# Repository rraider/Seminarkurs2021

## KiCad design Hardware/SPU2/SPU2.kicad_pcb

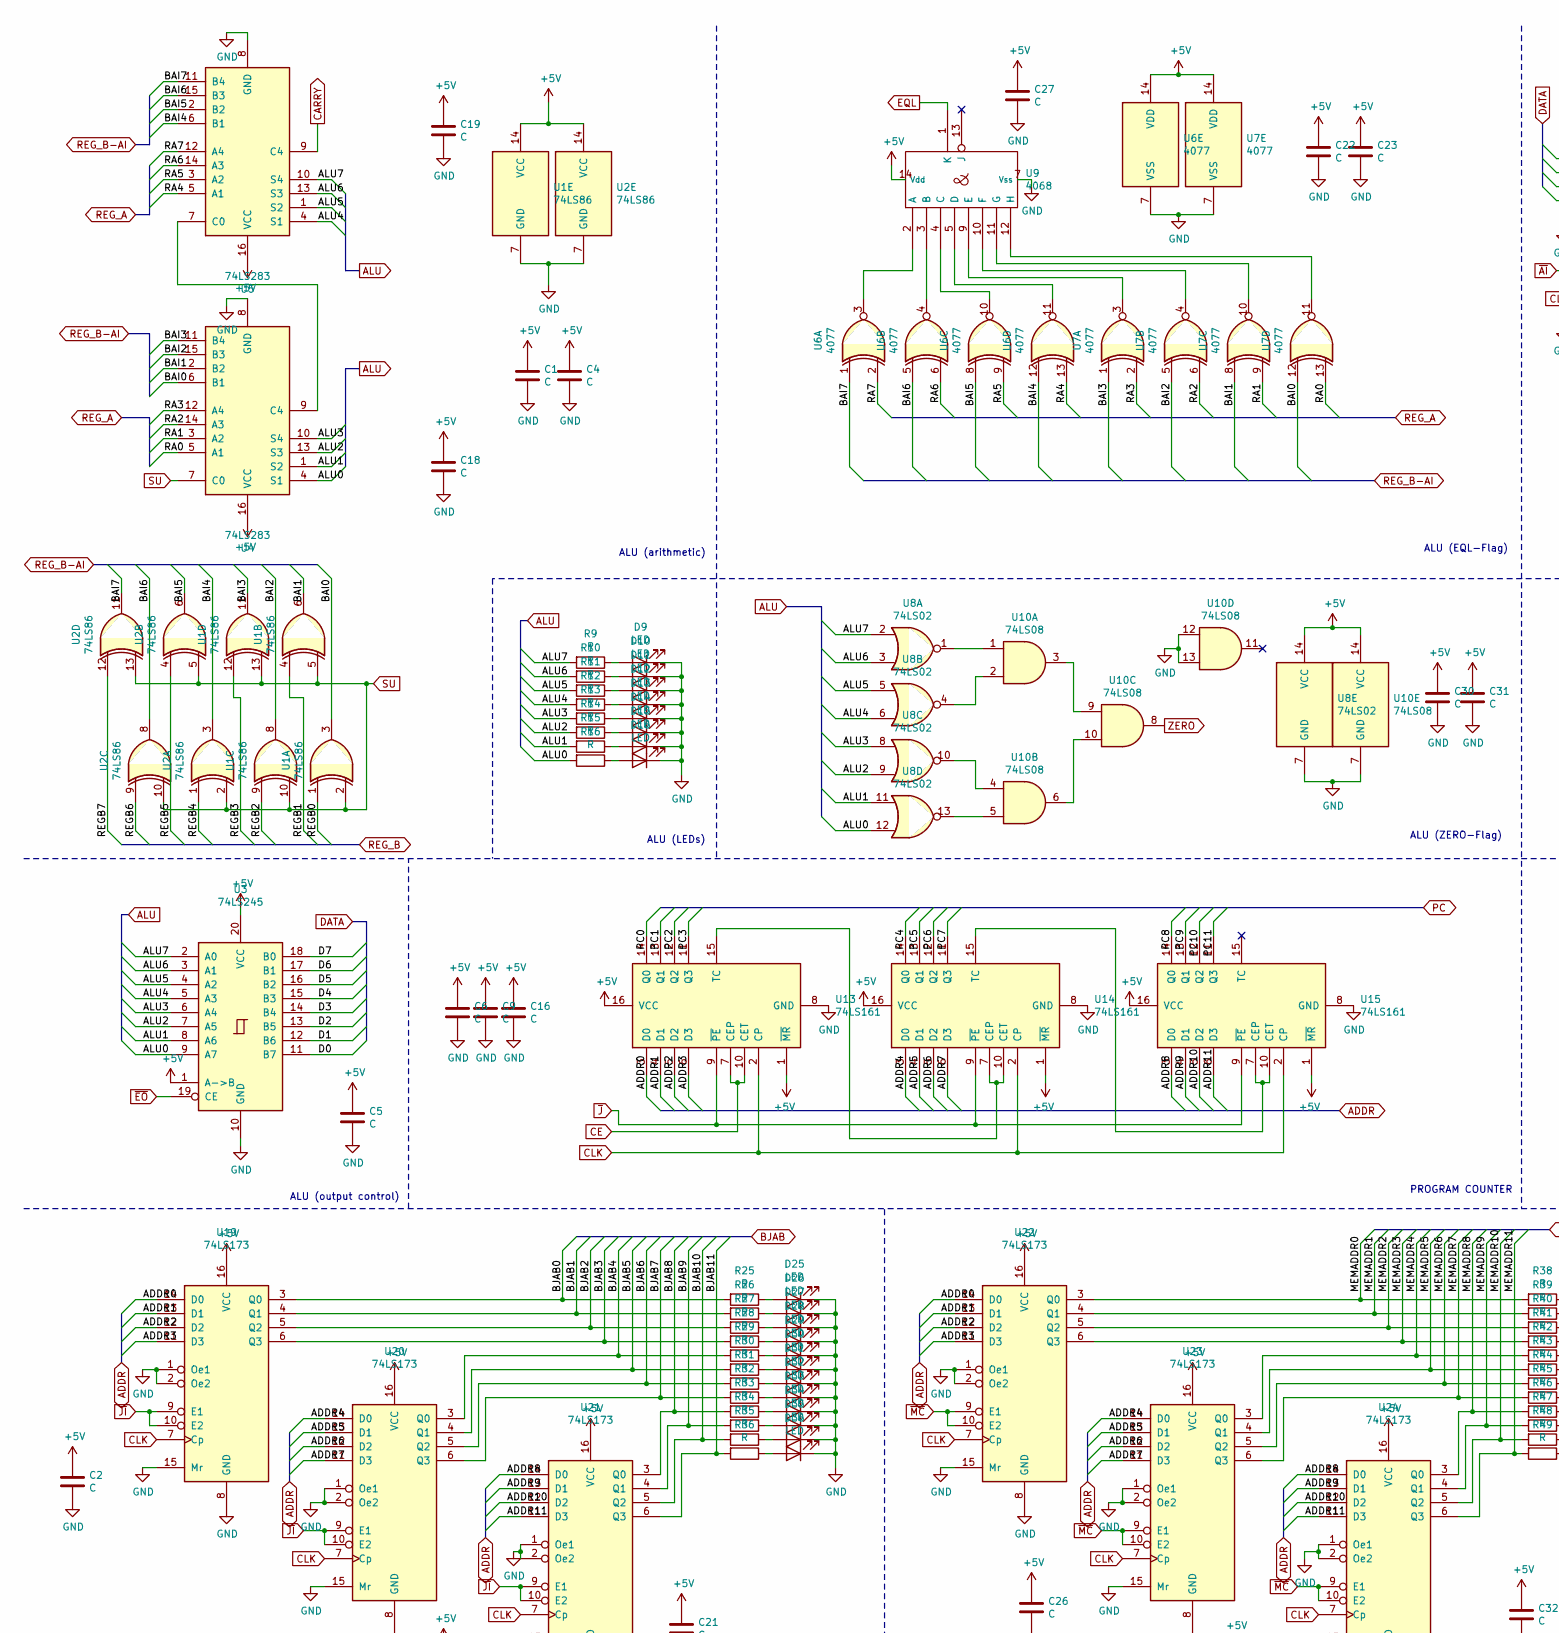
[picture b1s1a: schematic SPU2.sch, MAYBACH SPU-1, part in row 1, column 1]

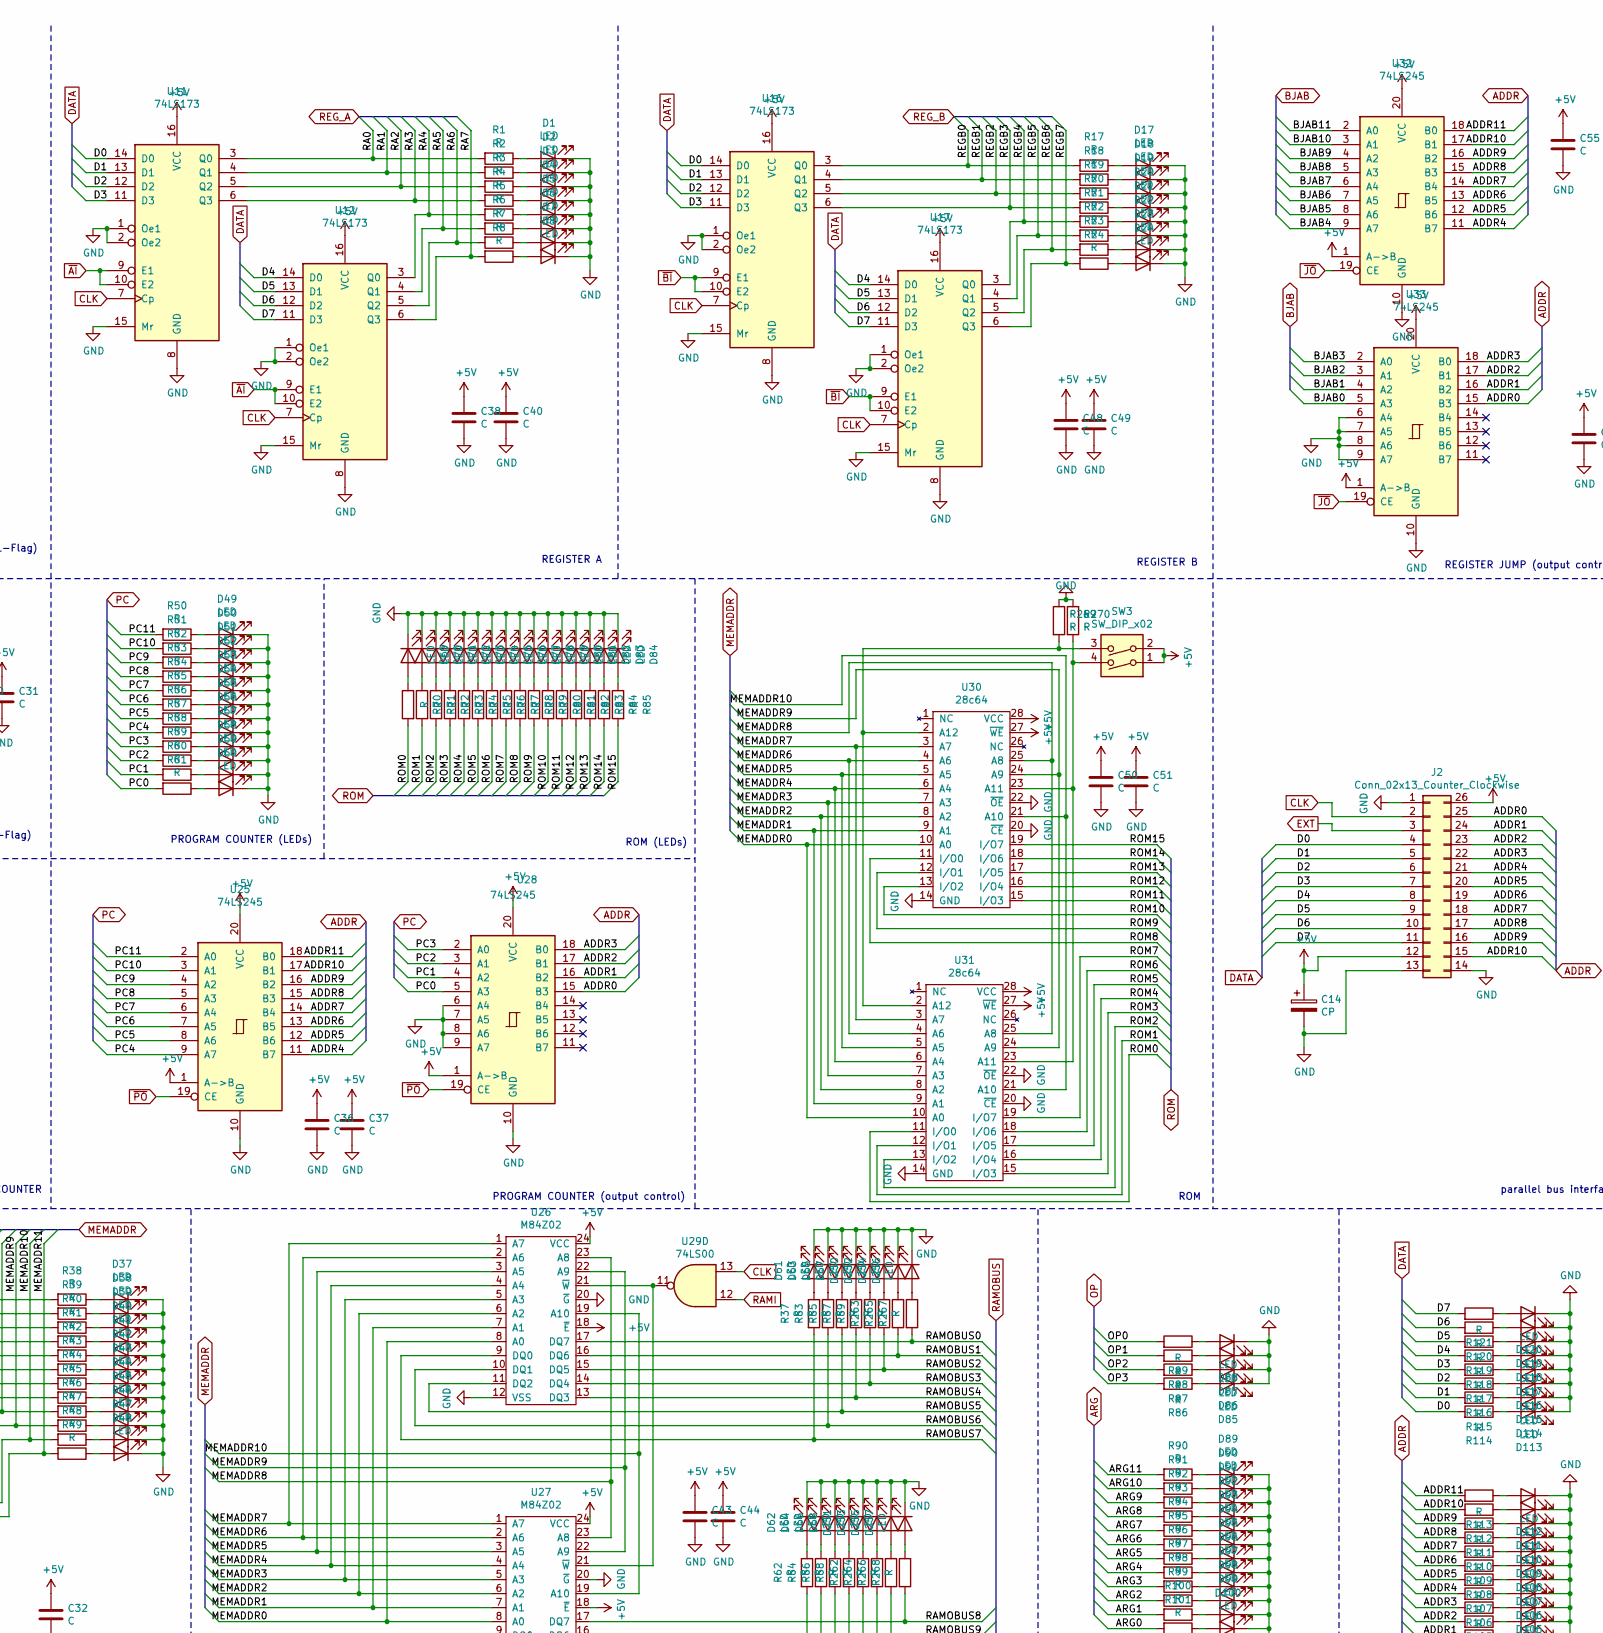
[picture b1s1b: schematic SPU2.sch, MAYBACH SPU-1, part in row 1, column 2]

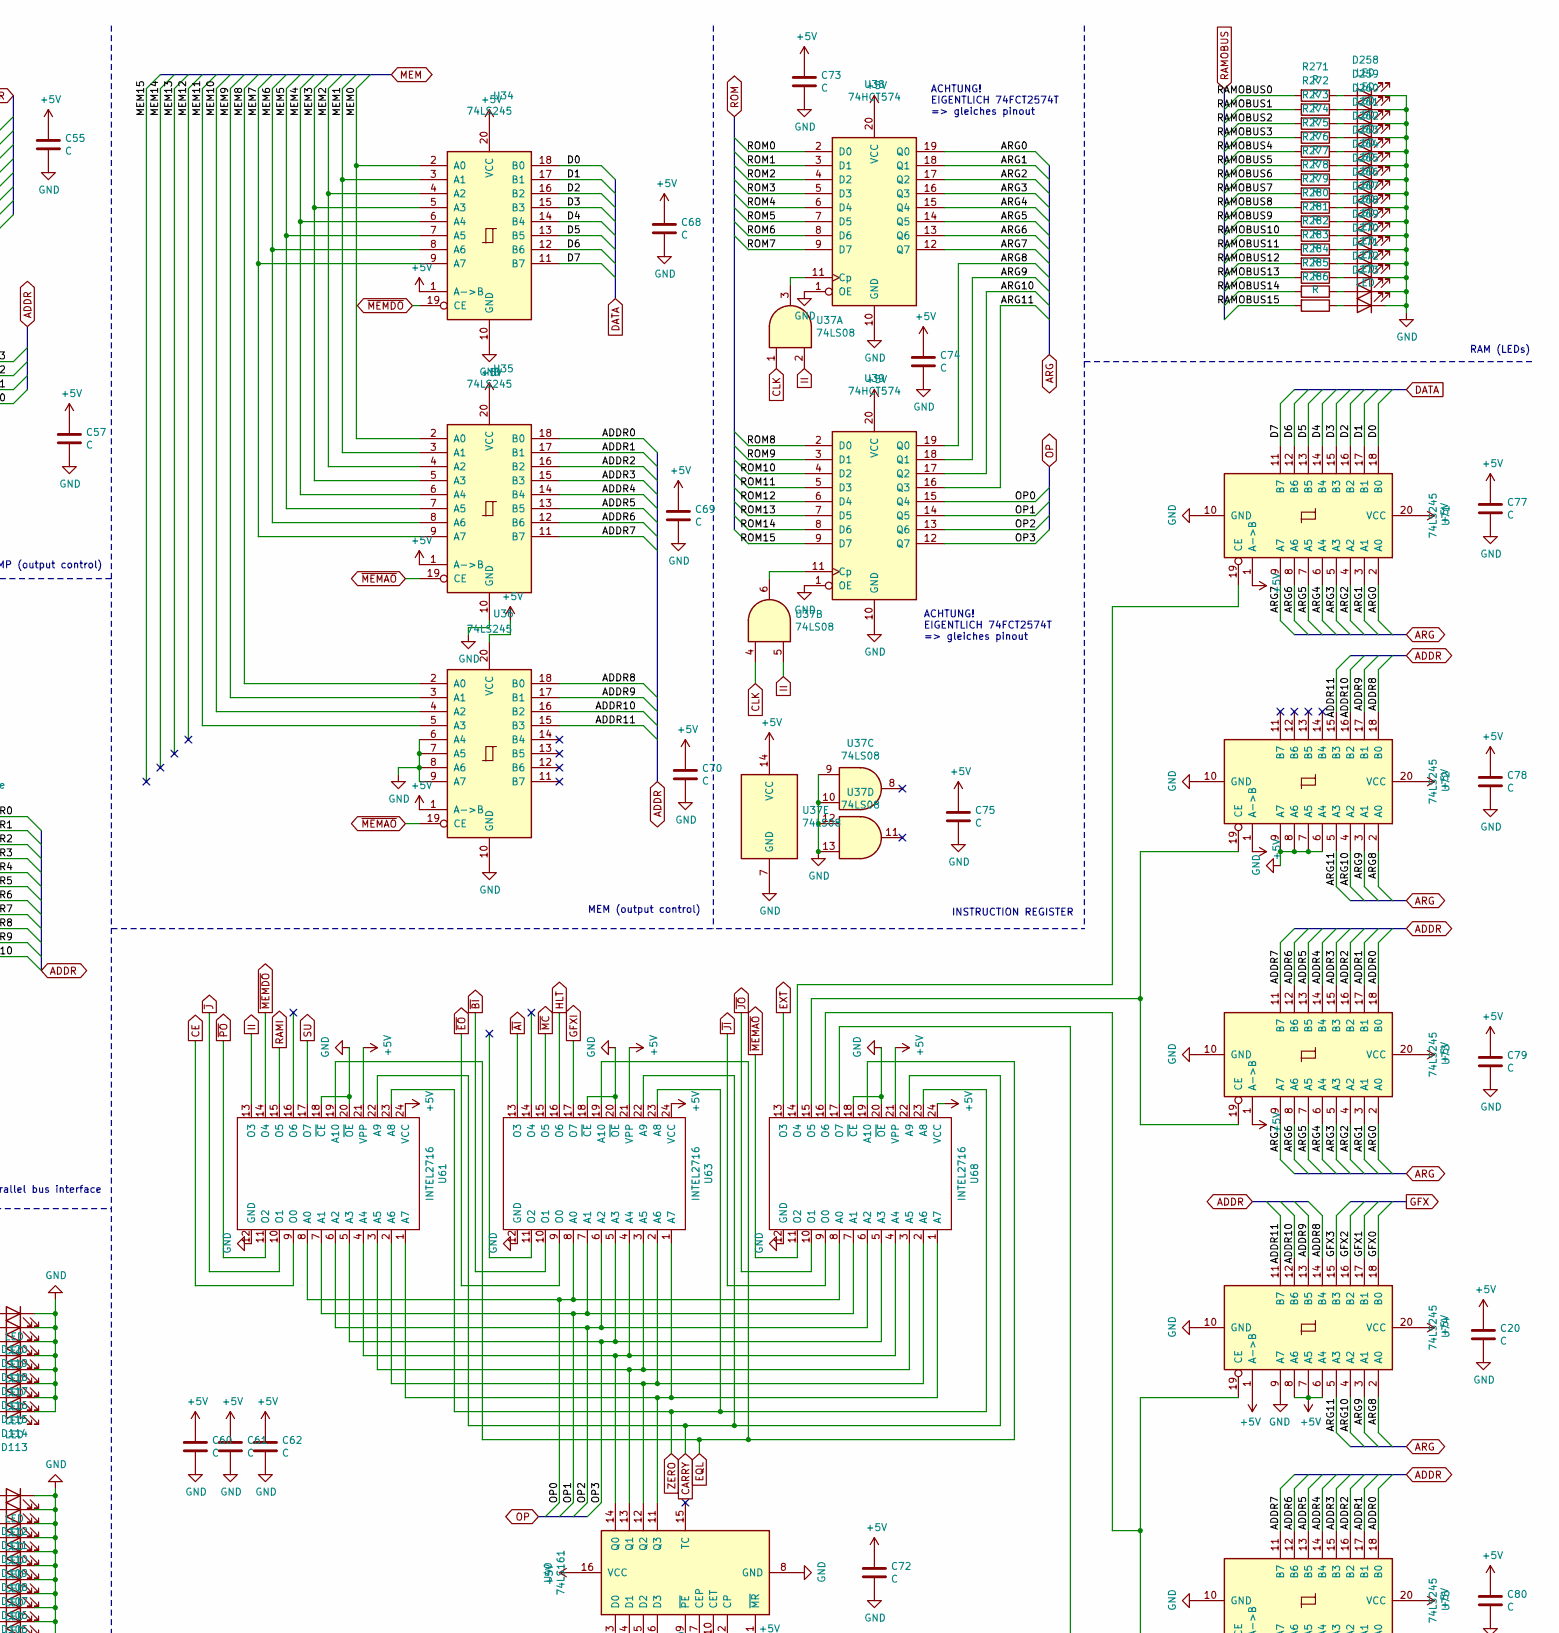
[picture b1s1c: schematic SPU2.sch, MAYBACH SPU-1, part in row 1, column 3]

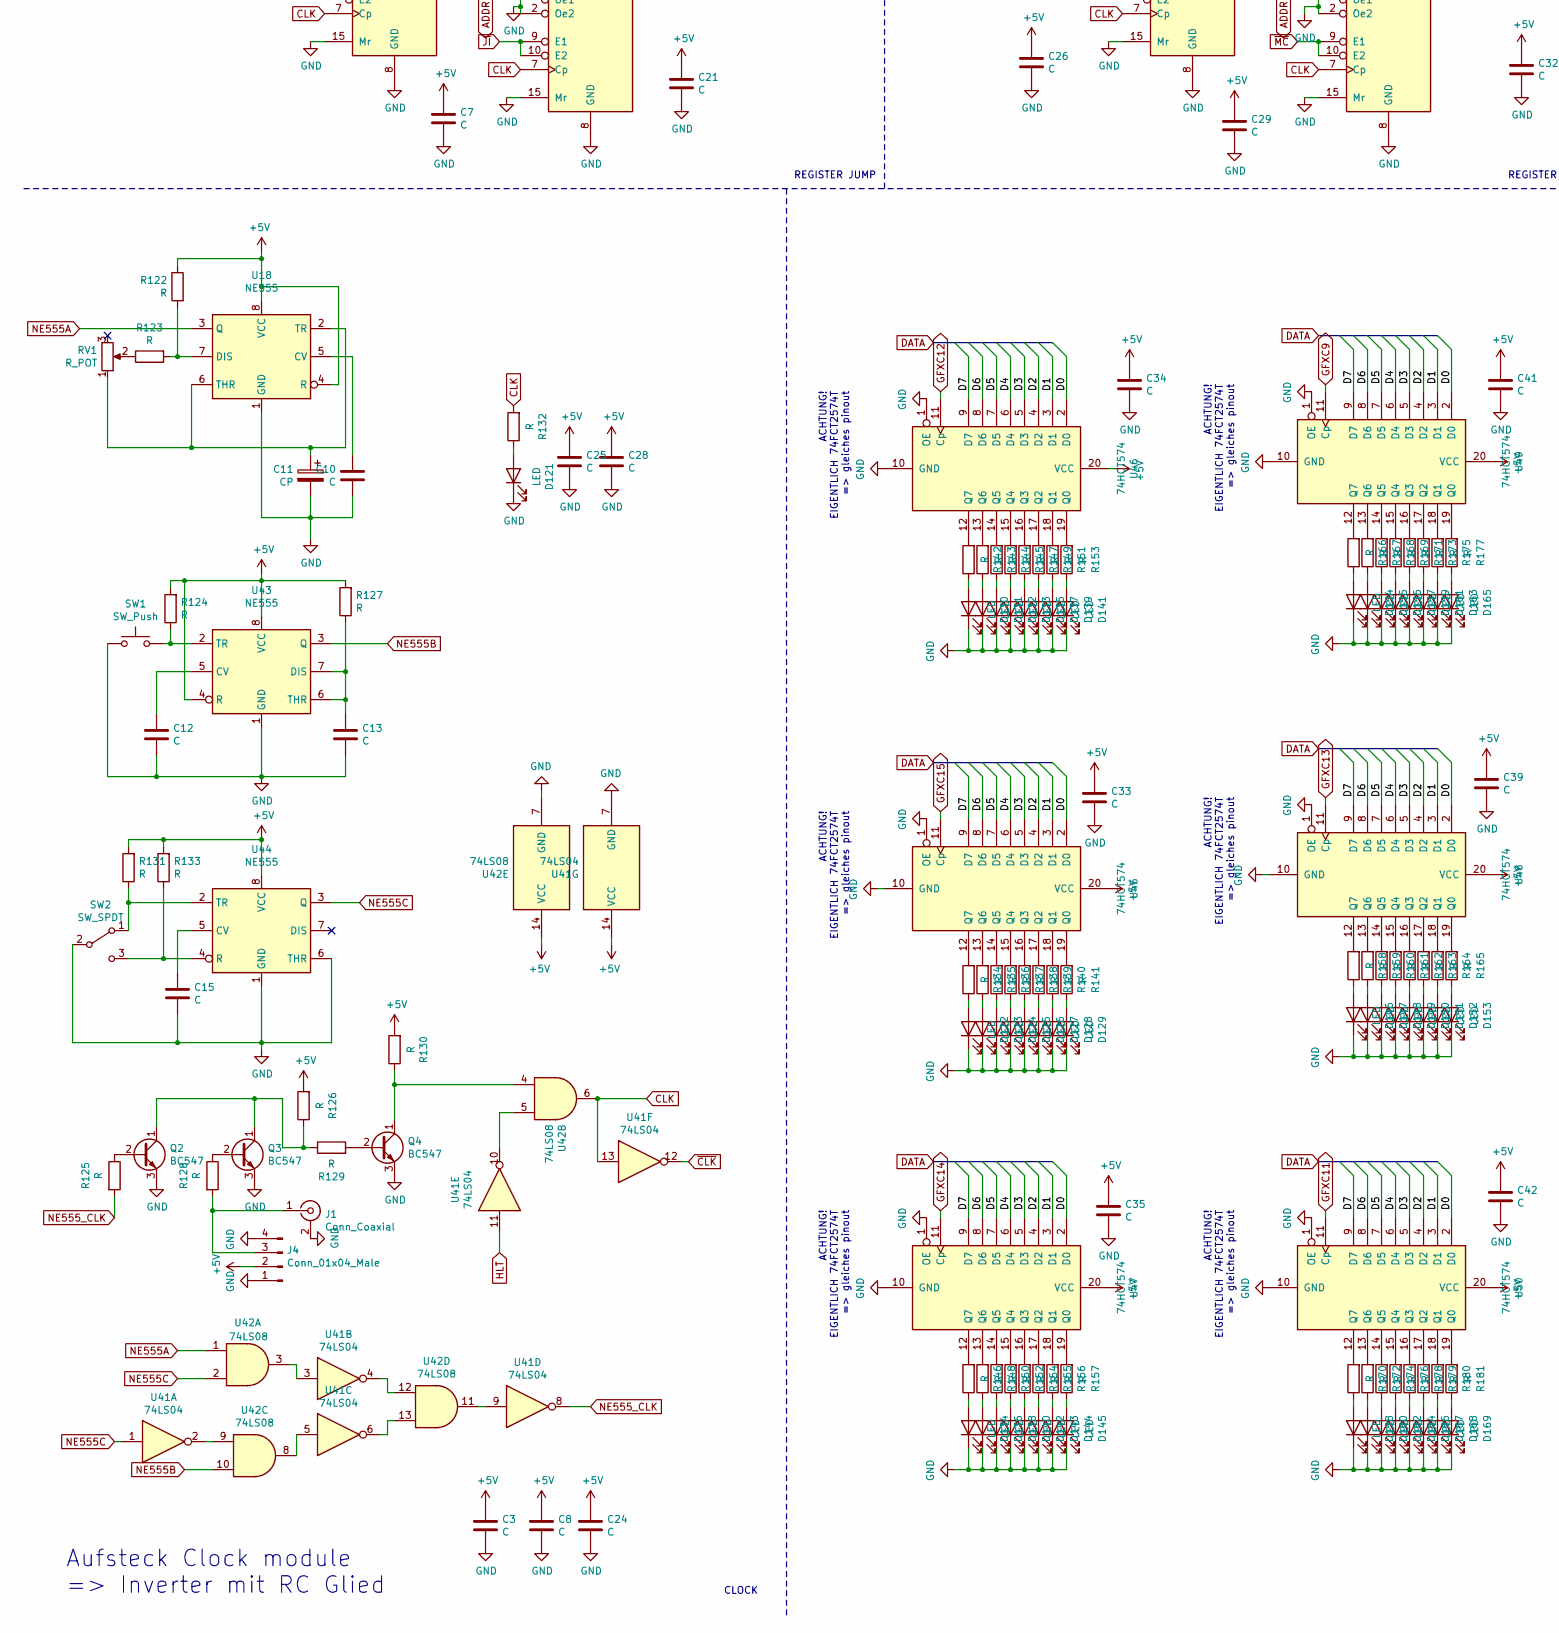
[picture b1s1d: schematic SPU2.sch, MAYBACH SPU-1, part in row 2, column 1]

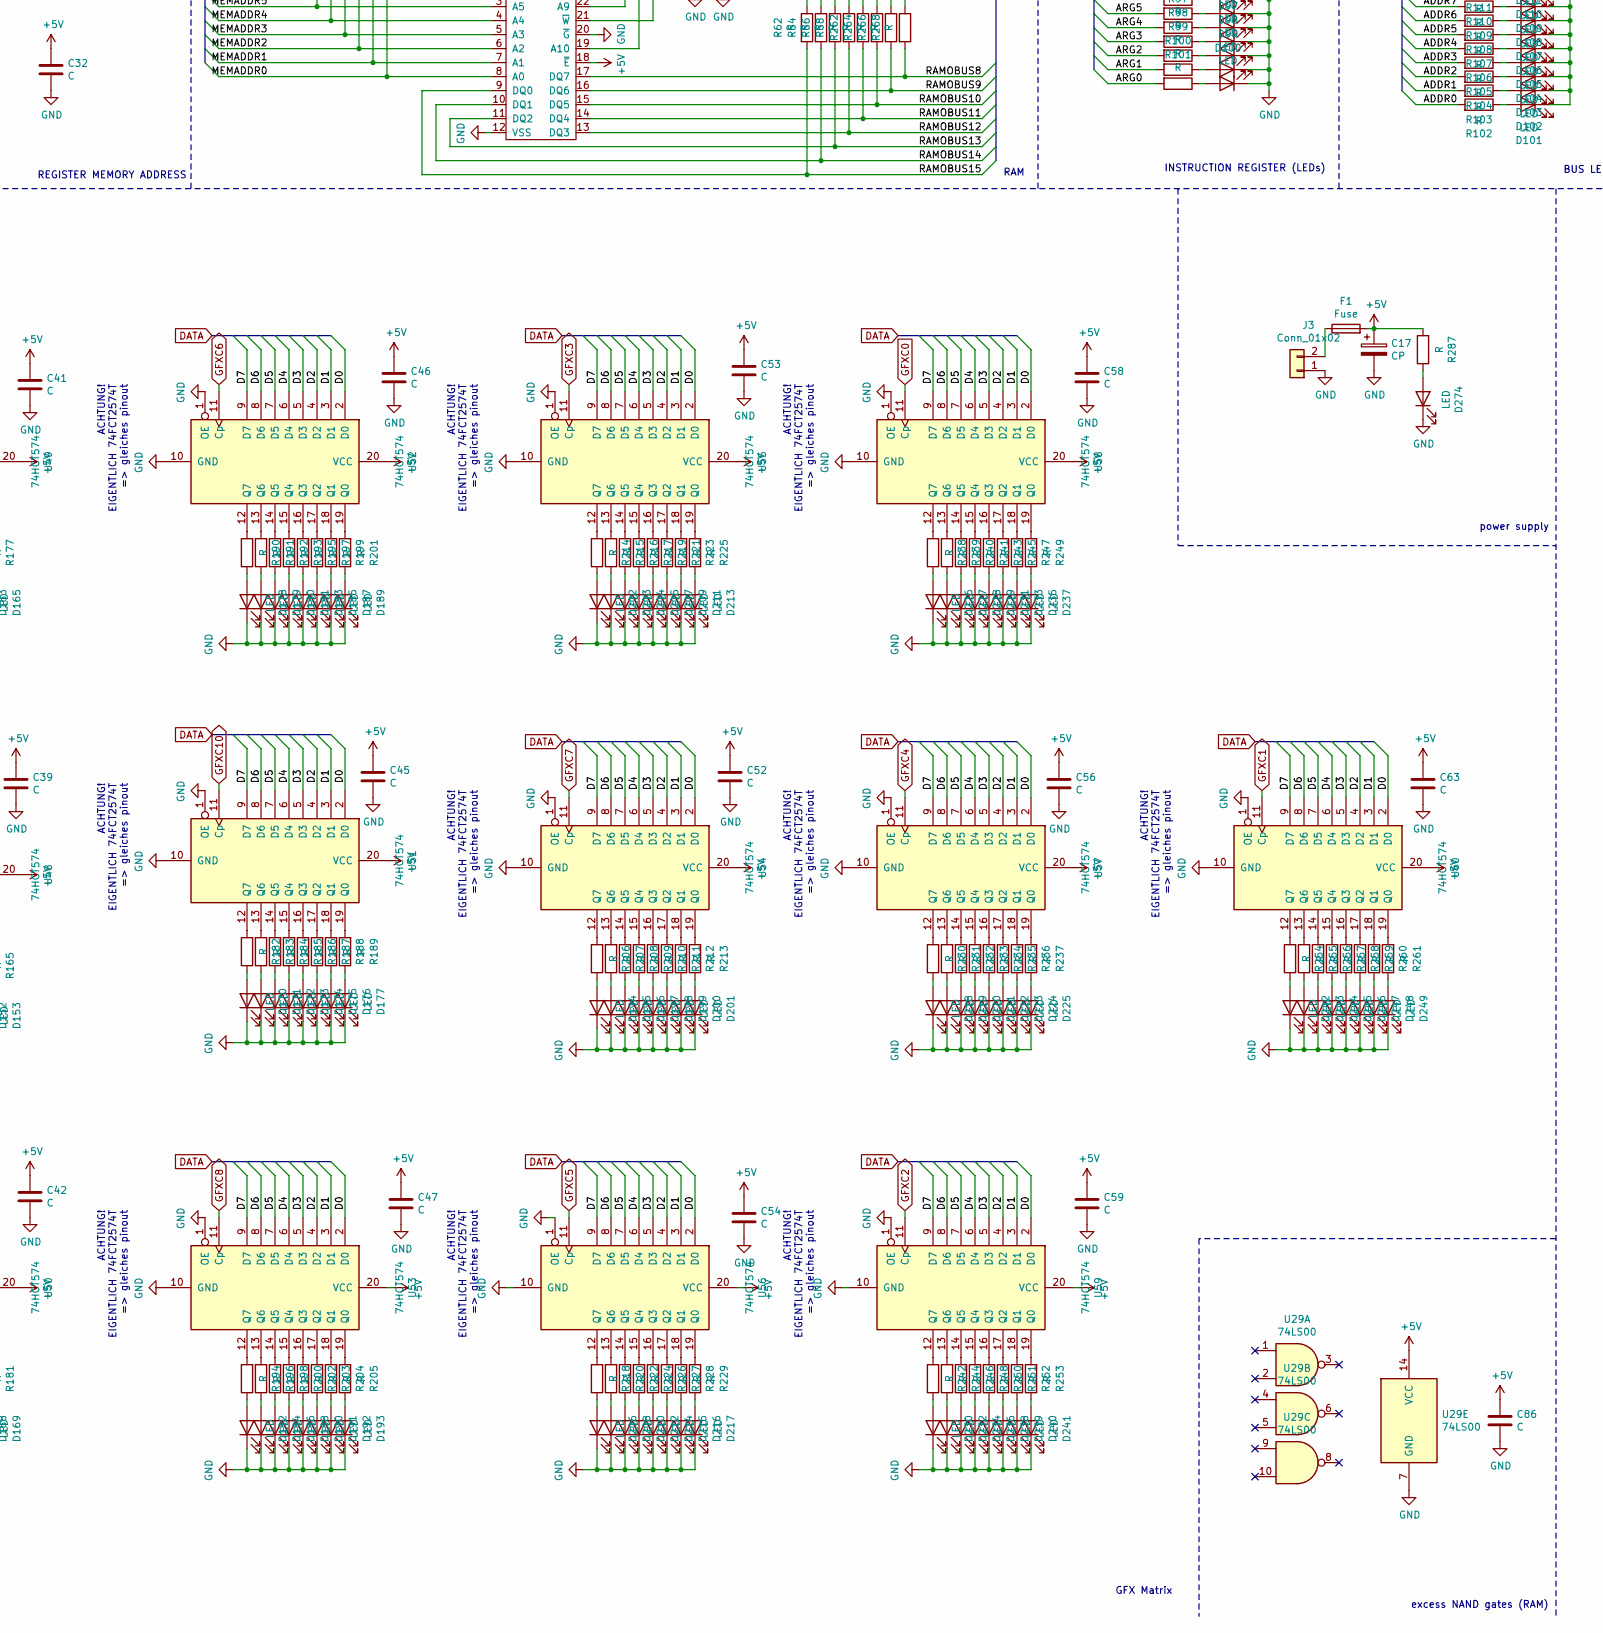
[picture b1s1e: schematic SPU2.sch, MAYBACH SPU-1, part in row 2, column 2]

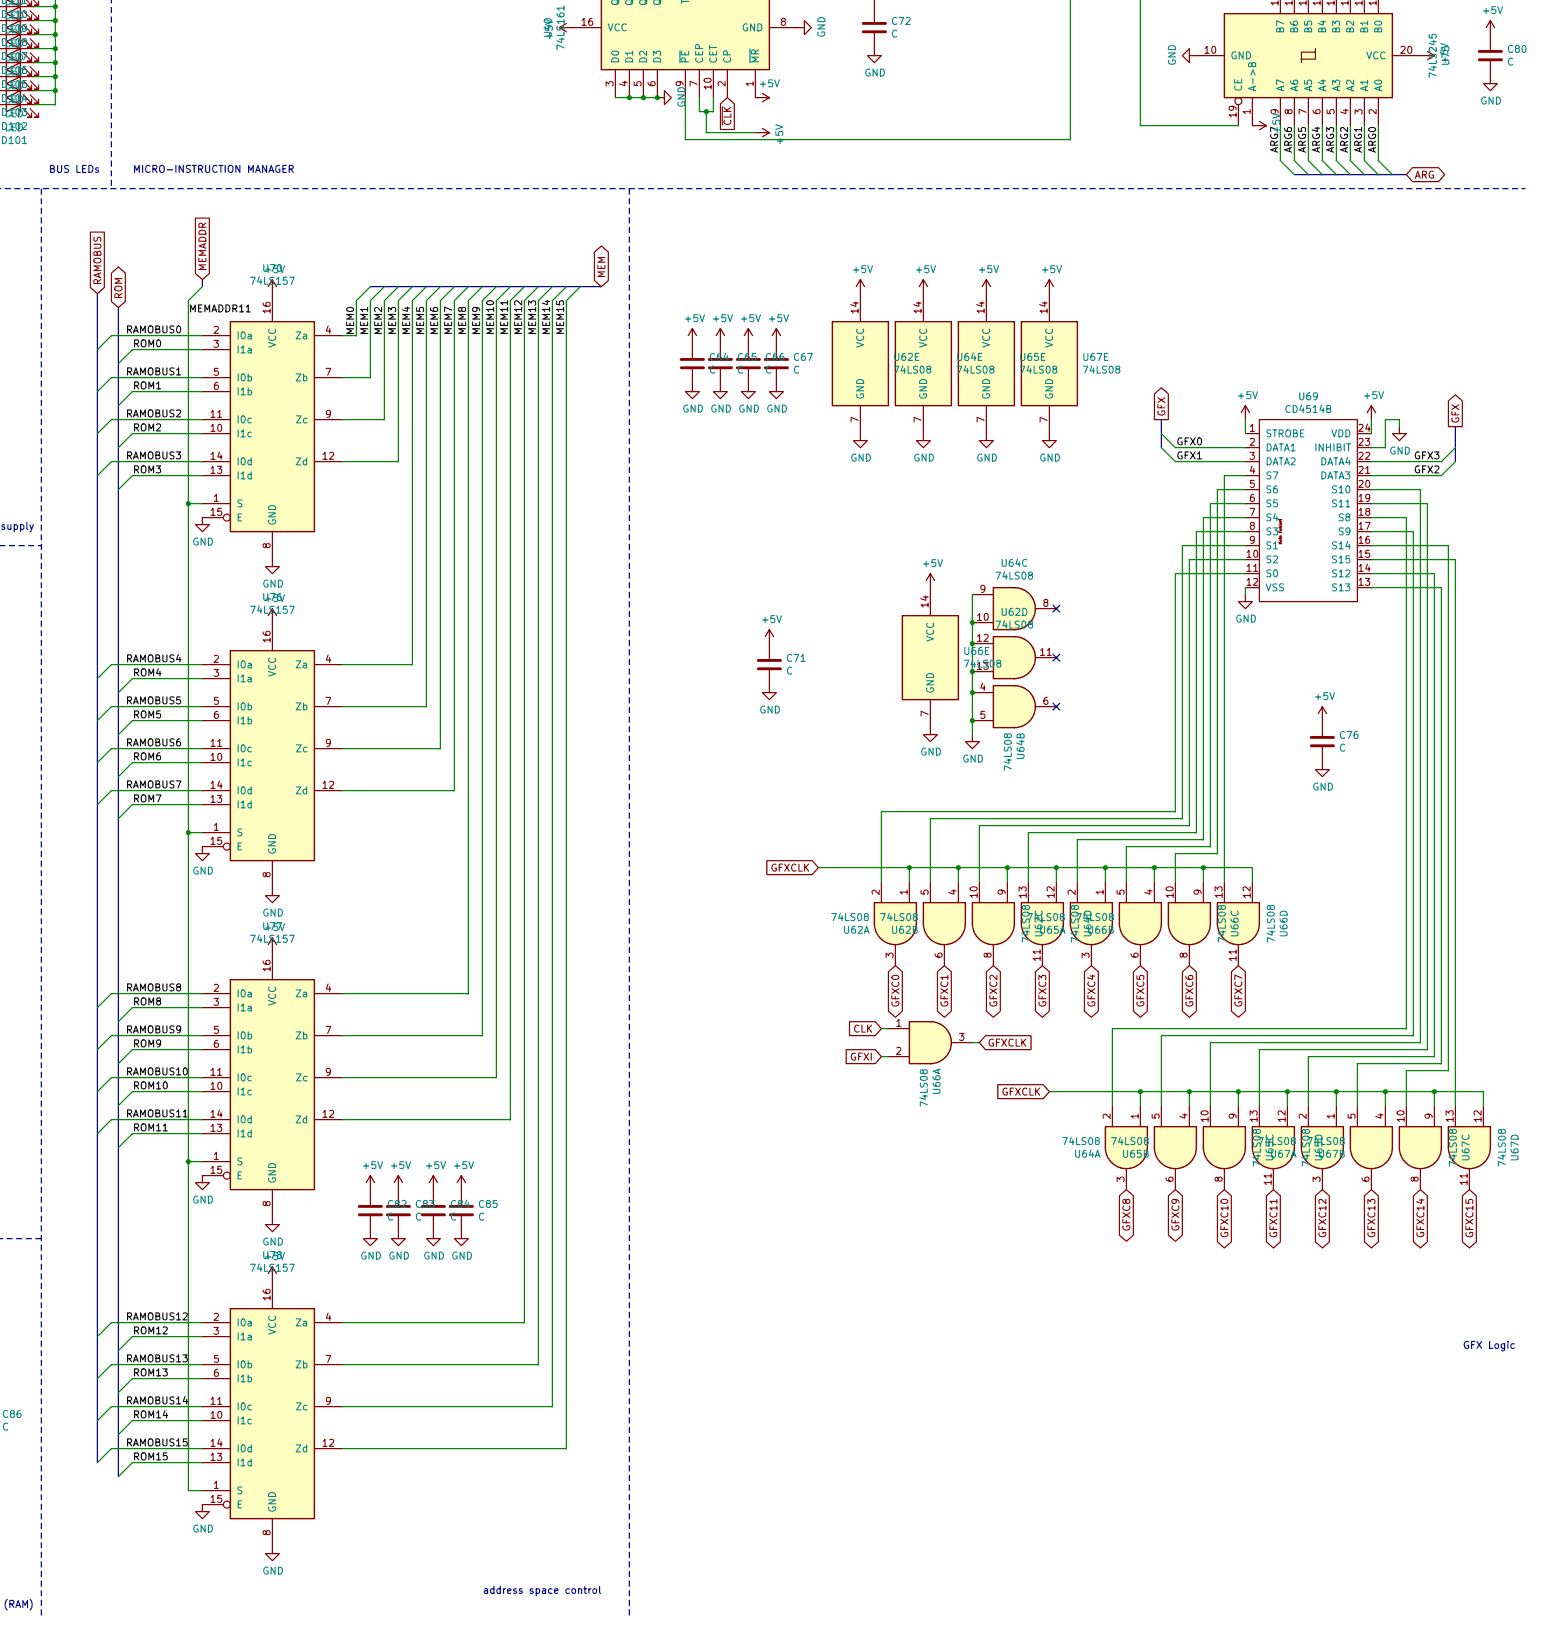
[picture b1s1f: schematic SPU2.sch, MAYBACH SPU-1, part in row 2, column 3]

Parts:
C1, C2, C3, C4, C5, C6, C7, C8, C9, C10, C12, C13, C15, C16, C18, C19, C20, C21, C22, C23, C24, C25, C26, C27, C28, C29, C30, C31, C32, C33, C34, C35, C36, C37, C38, C39, C40, C41, C42, C43, C44, C45, C46, C47, C48, C49, C50, C51, C52, C53, C54, C55, C56, C57, C58, C59, C60, C61, C62, C63, C64, C65, C66, C67, C68, C69, C70, C71, C72, C73, C74, C75, C76, C77, C78, C79, C80, C82, C83, C84, C85, C86: C; C_0805_2012Metric_Pad1.15x1.40mm_HandSolder
C11, C14, C17: CP; CP_EIA-6032-15_Kemet-U_Pad2.25x2.35mm_HandSolder
D1, D2, D3, D4, D5, D6, D7, D8, D9, D10, D11, D12, D13, D14, D15, D16, D17, D18, D19, D20, D21, D22, D23, D24, D25, D26, D27, D28, D29, D30, D31, D32, D33, D34, D35, D36, D37, D38, D39, D40, D41, D42, D43, D44, D45, D46, D47, D48, D49, D50, D51, D52, D53, D54, D55, D56, D57, D58, D59, D60, D61, D62, D63, D64, D65, D66, D67, D68, D69, D70, D71, D72, D73, D74, D75, D76, D77, D78, D79, D80, D81, D82, D83, D84, D85, D86, D87, D88, D89, D90, D91, D92, D93, D94, D95, D96, D97, D98, D99, D100, D101, D102, D103, D104, D105, D106, D107, D108, D109, D110, D111, D112, D113, D114, D115, D116, D117, D118, D119, D120, D121, D122, D123, D124, D125, D126, D127, D128, D129, D130, D131, D132, D133, D134, D135, D136, D137, D138, D139, D140, D141, D142, D143, D144, D145, D146, D147, D148, D149, D150, D151, D152, D153, D154, D155, D156, D157, D158, D159, D160, D161, D162, D163, D164, D165, D166, D167, D168, D169, D170, D171, D172, D173, D174, D175, D176, D177, D178, D179, D180, D181, D182, D183, D184, D185, D186, D187, D188, D189, D190, D191, D192, D193, D194, D195, D196, D197, D198, D199, D200, D201, D202, D203, D204, D205, D206, D207, D208, D209, D210, D211, D212, D213, D214, D215, D216, D217, D218, D219, D220, D221, D222, D223, D224, D225, D226, D227, D228, D229, D230, D231, D232, D233, D234, D235, D236, D237, D238, D239, D240, D241, D242, D243, D244, D245, D246, D247, D248, D249, D250, D251, D252, D253, D254, D255, D256, D257, D258, D259, D260, D261, D262, D263, D264, D265, D266, D267, D268, D269, D270, D271, D272, D273, D274: LED; LED_D5.0mm
F1: Fuse; Fuse_1812_4532Metric_Pad1.30x3.40mm_HandSolder
J1: Conn_Coaxial; SMA_Amphenol_132134-16_Vertical
J2: Conn_02x13_Counter_Clockwise; PinHeader_2x13_P2.54mm_Vertical
J3: Conn_01x02; AMASS_XT30U-F_1x02_P5.0mm_Vertical
J4: Conn_01x04_Male; PinHeader_1x04_P2.54mm_Vertical
Q2, Q3, Q4: BC547; TO-92_Inline
R1, R2, R3, R4, R5, R6, R7, R8, R9, R10, R11, R12, R13, R14, R15, R16, R17, R18, R19, R20, R21, R22, R23, R24, R25, R26, R27, R28, R29, R30, R31, R32, R33, R34, R35, R36, R37, R38, R39, R40, R41, R42, R43, R44, R45, R46, R47, R48, R49, R50, R51, R52, R53, R54, R55, R56, R57, R58, R59, R60, R61, R62, R63, R64, R65, R66, R67, R68, R69, R70, R71, R72, R73, R74, R75, R76, R77, R78, R79, R80, R81, R82, R83, R84, R85, R86, R87, R88, R89, R90, R91, R92, R93, R94, R95, R96, R97, R98, R99, R100, R101, R102, R103, R104, R105, R106, R107, R108, R109, R110, R111, R112, R113, R114, R115, R116, R117, R118, R119, R120, R121, R122, R123, R124, R125, R126, R127, R128, R129, R130, R131, R132, R133, R134, R135, R136, R137, R138, R139, R140, R141, R142, R143, R144, R145, R146, R147, R148, R149, R150, R151, R152, R153, R154, R155, R156, R157, R158, R159, R160, R161, R162, R163, R164, R165, R166, R167, R168, R169, R170, R171, R172, R173, R174, R175, R176, R177, R178, R179, R180, R181, R182, R183, R184, R185, R186, R187, R188, R189, R190, R191, R192, R193, R194, R195, R196, R197, R198, R199, R200, R201, R202, R203, R204, R205, R206, R207, R208, R209, R210, R211, R212, R213, R214, R215, R216, R217, R218, R219, R220, R221, R222, R223, R224, R225, R226, R227, R228, R229, R230, R231, R232, R233, R234, R235, R236, R237, R238, R239, R240, R241, R242, R243, R244, R245, R246, R247, R248, R249, R250, R251, R252, R253, R254, R255, R256, R257, R258, R259, R260, R261, R262, R263, R264, R265, R266, R267, R268, R269, R270, R271, R272, R273, R274, R275, R276, R277, R278, R279, R280, R281, R282, R283, R284, R285, R286, R287: R; R_0805_2012Metric_Pad1.15x1.40mm_HandSolder
RV1: R_POT; Potentiometer_Piher_PT-15-V02_Vertical
SW1: SW_Push; Panasonic_EVQPUK_EVQPUB
SW2: SW_SPDT; SW_CuK_OS102011MA1QN1_SPDT_Angled
SW3: SW_DIP_x02; SW_DIP_SPSTx02_Slide_9.78x7.26mm_W7.62mm_P2.54mm
U1, U2: 74LS86; DIP-14_W7.62mm_Socket_LongPads
U3, U25, U28, U32, U33, U34, U35, U36, U71, U72, U73, U74, U75: 74LS245; DIP-20_W7.62mm_Socket_LongPads
U4, U5: 74LS283; DIP-16_W7.62mm_Socket_LongPads
U6, U7: 4077; DIP-14_W7.62mm_Socket_LongPads
U8: 74LS02; DIP-14_W7.62mm_Socket_LongPads
U9: 4068; DIP-14_W7.62mm_Socket_LongPads
U10, U37, U42, U62, U64, U65, U66, U67: 74LS08; DIP-14_W7.62mm_Socket_LongPads
U11, U12, U16, U17, U19, U20, U21, U22, U23, U24: 74LS173; DIP-16_W7.62mm_Socket_LongPads
U13, U14, U15, U40: 74LS161; DIP-16_W7.62mm_Socket_LongPads
U18, U43, U44: NE555; DIP-8_W7.62mm
U26, U27: M84Z02; DIP-24_W15.24mm_Socket_LongPads
U29: 74LS00; DIP-14_W7.62mm_Socket_LongPads
U30, U31: 28c64; DIP-28_W15.24mm_Socket_LongPads
U38, U39, U45, U46, U47, U48, U49, U50, U51, U52, U53, U54, U55, U56, U57, U58, U59, U60: 74HCT574; SOIC-20W_7.5x12.8mm_P1.27mm
U41: 74LS04; DIP-14_W7.62mm_Socket_LongPads
U61, U63, U68: INTEL2716; DIP-24_W15.24mm_Socket_LongPads
U69: CD4514B; DIP-24_W15.24mm_Socket_LongPads
U70, U76, U77, U78: 74LS157; DIP-16_W7.62mm_Socket_LongPads

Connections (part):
+5V: C1.1, C2.1, C3.1, C4.1, C5.1, C6.1, C7.1, C8.1, C9.1, C14.1, C16.1, C17.1, C18.1, C19.1, C20.1, C21.1, C22.1, C23.1, C24.1, C25.1, C26.1, C27.1, C28.1, C29.1, C30.1, C31.1, C32.1, C33.1, C34.1, C35.1, C36.1, C37.1, C38.1, C39.1, C40.1, C41.1, C42.1, C43.1, C44.1, C45.1, C46.1, C47.1, C48.1, C49.1, C50.1, C51.1, C52.1, C53.1, C54.1, C55.1, C56.1, C57.1, C58.1, C59.1, C60.1, C61.1, C62.1, C63.1, C64.1, C65.1, C66.1, C67.1, C68.1, C69.1, C70.1, C71.1, C72.1, C73.1, C74.1, C75.1, C76.1, C77.1, C78.1, C79.1, C80.1, C82.1, C83.1, C84.1, C85.1, C86.1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
/ADDR0: J2.25, R102.2, U13.3 (D0), U19.14 (D0), U22.14 (D0), U28.15 (B3), U33.15 (B3), U35.18 (B0), U73.18 (B0), U75.18 (B0)
/ADDR1: J2.24, R103.2, U13.4 (D1), U19.13 (D1), U22.13 (D1), U28.16 (B2), U33.16 (B2), U35.17 (B1), U73.17 (B1), U75.17 (B1)
/ADDR2: J2.23, R104.2, U13.5 (D2), U19.12 (D2), U22.12 (D2), U28.17 (B1), U33.17 (B1), U35.16 (B2), U73.16 (B2), U75.16 (B2)
/ADDR3: J2.22, R105.2, U13.6 (D3), U19.11 (D3), U22.11 (D3), U28.18 (B0), U33.18 (B0), U35.15 (B3), U73.15 (B3), U75.15 (B3)
/ADDR4: J2.21, R106.2, U14.3 (D0), U20.14 (D0), U23.14 (D0), U25.11 (B7), U32.11 (B7), U35.14 (B4), U73.14 (B4), U75.14 (B4)
/ADDR5: J2.20, R107.2, U14.4 (D1), U20.13 (D1), U23.13 (D1), U25.12 (B6), U32.12 (B6), U35.13 (B5), U73.13 (B5), U75.13 (B5)
/ADDR6: J2.19, R108.2, U14.5 (D2), U20.12 (D2), U23.12 (D2), U25.13 (B5), U32.13 (B5), U35.12 (B6), U73.12 (B6), U75.12 (B6)
/ADDR7: J2.18, R109.2, U14.6 (D3), U20.11 (D3), U23.11 (D3), U25.14 (B4), U32.14 (B4), U35.11 (B7), U73.11 (B7), U75.11 (B7)
/ADDR8: J2.17, R110.2, U15.3 (D0), U21.14 (D0), U24.14 (D0), U25.15 (B3), U32.15 (B3), U36.18 (B0), U72.18 (B0), U74.14 (B4)
/ADDR9: J2.16, R111.2, U15.4 (D1), U21.13 (D1), U24.13 (D1), U25.16 (B2), U32.16 (B2), U36.17 (B1), U72.17 (B1), U74.13 (B5)
/ADDR10: J2.15, R112.2, U15.5 (D2), U21.12 (D2), U24.12 (D2), U25.17 (B1), U32.17 (B1), U36.16 (B2), U72.16 (B2), U74.12 (B6)
/ADDR11: R113.2, U15.6 (D3), U21.11 (D3), U24.11 (D3), U25.18 (B0), U32.18 (B0), U36.15 (B3), U72.15 (B3), U74.11 (B7)
/ALU0: R16.2, U3.9 (A7), U4.4 (S1), U8.12
/ALU1: R15.2, U3.8 (A6), U4.1 (S2), U8.11
/ALU2: R14.2, U3.7 (A5), U4.13 (S3), U8.9
/ALU3: R13.2, U3.6 (A4), U4.10 (S4), U8.8
/ALU4: R12.2, U3.5 (A3), U5.4 (S1), U8.6
/ALU5: R11.2, U3.4 (A2), U5.1 (S2), U8.5
/ALU6: R10.2, U3.3 (A1), U5.13 (S3), U8.3
/ALU7: R9.2, U3.2 (A0), U5.10 (S4), U8.2
/ARG0: R101.2, U38.19 (Q0), U71.2 (A0), U73.2 (A0), U75.2 (A0)
/ARG1: R100.2, U38.18 (Q1), U71.3 (A1), U73.3 (A1), U75.3 (A1)
/ARG2: R99.2, U38.17 (Q2), U71.4 (A2), U73.4 (A2), U75.4 (A2)
/ARG3: R98.2, U38.16 (Q3), U71.5 (A3), U73.5 (A3), U75.5 (A3)
/ARG4: R97.2, U38.15 (Q4), U71.6 (A4), U73.6 (A4), U75.6 (A4)
/ARG5: R96.2, U38.14 (Q5), U71.7 (A5), U73.7 (A5), U75.7 (A5)
/ARG6: R95.2, U38.13 (Q6), U71.8 (A6), U73.8 (A6), U75.8 (A6)
/ARG7: R94.2, U38.12 (Q7), U71.9 (A7), U73.9 (A7), U75.9 (A7)
/ARG8: R93.2, U39.19 (Q0), U72.2 (A0), U74.2 (A0)
/ARG9: R92.2, U39.18 (Q1), U72.3 (A1), U74.3 (A1)
/ARG10: R91.2, U39.17 (Q2), U72.4 (A2), U74.4 (A2)
/ARG11: R90.2, U39.16 (Q3), U72.5 (A3), U74.5 (A3)
/BAI0: U1.3, U4.6 (B1), U7.12
/BAI1: U1.6, U4.2 (B2), U7.8
/BAI2: U1.8, U4.15 (B3), U7.5
/BAI3: U1.11, U4.11 (B4), U7.1
/BAI4: U2.3, U5.6 (B1), U6.12
/BAI5: U2.6, U5.2 (B2), U6.8
/BAI6: U2.8, U5.15 (B3), U6.5
/BAI7: U2.11, U5.11 (B4), U6.1
/BJAB0: R25.2, U19.3 (Q0), U33.5 (A3)
/BJAB1: R26.2, U19.4 (Q1), U33.4 (A2)
/BJAB2: R27.2, U19.5 (Q2), U33.3 (A1)
/BJAB3: R28.2, U19.6 (Q3), U33.2 (A0)
/BJAB4: R29.2, U20.3 (Q0), U32.9 (A7)
/BJAB5: R30.2, U20.4 (Q1), U32.8 (A6)
/BJAB6: R31.2, U20.5 (Q2), U32.7 (A5)
/BJAB7: R32.2, U20.6 (Q3), U32.6 (A4)
/BJAB8: R33.2, U21.3 (Q0), U32.5 (A3)
/BJAB9: R34.2, U21.4 (Q1), U32.4 (A2)
/BJAB10: R35.2, U21.5 (Q2), U32.3 (A1)
/BJAB11: R36.2, U21.6 (Q3), U32.2 (A0)
/D0: J2.4, R114.2, U3.11 (B7), U11.14 (D0), U16.14 (D0), U34.18 (B0), U45.2 (D0), U46.2 (D0), U47.2 (D0), U48.2 (D0), U49.2 (D0), U50.2 (D0), U51.2 (D0), U52.2 (D0), U53.2 (D0), U54.2 (D0), U55.2 (D0), U56.2 (D0), U57.2 (D0), U58.2 (D0), U59.2 (D0), U60.2 (D0), U71.18 (B0)
/D1: J2.5, R115.2, U3.12 (B6), U11.13 (D1), U16.13 (D1), U34.17 (B1), U45.3 (D1), U46.3 (D1), U47.3 (D1), U48.3 (D1), U49.3 (D1), U50.3 (D1), U51.3 (D1), U52.3 (D1), U53.3 (D1), U54.3 (D1), U55.3 (D1), U56.3 (D1), U57.3 (D1), U58.3 (D1), U59.3 (D1), U60.3 (D1), U71.17 (B1)
/D2: J2.6, R116.2, U3.13 (B5), U11.12 (D2), U16.12 (D2), U34.16 (B2), U45.4 (D2), U46.4 (D2), U47.4 (D2), U48.4 (D2), U49.4 (D2), U50.4 (D2), U51.4 (D2), U52.4 (D2), U53.4 (D2), U54.4 (D2), U55.4 (D2), U56.4 (D2), U57.4 (D2), U58.4 (D2), U59.4 (D2), U60.4 (D2), U71.16 (B2)
/D3: J2.7, R117.2, U3.14 (B4), U11.11 (D3), U16.11 (D3), U34.15 (B3), U45.5 (D3), U46.5 (D3), U47.5 (D3), U48.5 (D3), U49.5 (D3), U50.5 (D3), U51.5 (D3), U52.5 (D3), U53.5 (D3), U54.5 (D3), U55.5 (D3), U56.5 (D3), U57.5 (D3), U58.5 (D3), U59.5 (D3), U60.5 (D3), U71.15 (B3)
/D4: J2.8, R118.2, U3.15 (B3), U12.14 (D0), U17.14 (D0), U34.14 (B4), U45.6 (D4), U46.6 (D4), U47.6 (D4), U48.6 (D4), U49.6 (D4), U50.6 (D4), U51.6 (D4), U52.6 (D4), U53.6 (D4), U54.6 (D4), U55.6 (D4), U56.6 (D4), U57.6 (D4), U58.6 (D4), U59.6 (D4), U60.6 (D4), U71.14 (B4)
/D5: J2.9, R119.2, U3.16 (B2), U12.13 (D1), U17.13 (D1), U34.13 (B5), U45.7 (D5), U46.7 (D5), U47.7 (D5), U48.7 (D5), U49.7 (D5), U50.7 (D5), U51.7 (D5), U52.7 (D5), U53.7 (D5), U54.7 (D5), U55.7 (D5), U56.7 (D5), U57.7 (D5), U58.7 (D5), U59.7 (D5), U60.7 (D5), U71.13 (B5)
/D6: J2.10, R120.2, U3.17 (B1), U12.12 (D2), U17.12 (D2), U34.12 (B6), U45.8 (D6), U46.8 (D6), U47.8 (D6), U48.8 (D6), U49.8 (D6), U50.8 (D6), U51.8 (D6), U52.8 (D6), U53.8 (D6), U54.8 (D6), U55.8 (D6), U56.8 (D6), U57.8 (D6), U58.8 (D6), U59.8 (D6), U60.8 (D6), U71.12 (B6)
/D7: J2.11, R121.2, U3.18 (B0), U12.11 (D3), U17.11 (D3), U34.11 (B7), U45.9 (D7), U46.9 (D7), U47.9 (D7), U48.9 (D7), U49.9 (D7), U50.9 (D7), U51.9 (D7), U52.9 (D7), U53.9 (D7), U54.9 (D7), U55.9 (D7), U56.9 (D7), U57.9 (D7), U58.9 (D7), U59.9 (D7), U60.9 (D7), U71.11 (B7)
/GFX0: U69.2 (DATA1), U74.18 (B0)
/GFX1: U69.3 (DATA2), U74.17 (B1)
/GFX2: U69.21 (DATA3), U74.16 (B2)
/GFX3: U69.22 (DATA4), U74.15 (B3)
/MEM0: U34.2 (A0), U35.2 (A0), U70.4 (Za)
/MEM1: U34.3 (A1), U35.3 (A1), U70.7 (Zb)
/MEM2: U34.4 (A2), U35.4 (A2), U70.9 (Zc)
/MEM3: U34.5 (A3), U35.5 (A3), U70.12 (Zd)
/MEM4: U34.6 (A4), U35.6 (A4), U76.4 (Za)
/MEM5: U34.7 (A5), U35.7 (A5), U76.7 (Zb)
/MEM6: U34.8 (A6), U35.8 (A6), U76.9 (Zc)
/MEM7: U34.9 (A7), U35.9 (A7), U76.12 (Zd)
/MEM8: U36.2 (A0), U77.4 (Za)
/MEM9: U36.3 (A1), U77.7 (Zb)
/MEM10: U36.4 (A2), U77.9 (Zc)
/MEM11: U36.5 (A3), U77.12 (Zd)
/MEM12: U78.4 (Za)
/MEM13: U78.7 (Zb)
/MEM14: U78.9 (Zc)
/MEM15: U78.12 (Zd)
/MEMADDR0: R38.2, U22.3 (Q0), U26.8 (A0), U27.8 (A0), U30.10 (A0), U31.10 (A0)
/MEMADDR1: R39.2, U22.4 (Q1), U26.7 (A1), U27.7 (A1), U30.9 (A1), U31.9 (A1)
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
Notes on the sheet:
ALU (EQL-Flag)
ALU (ZERO-Flag)
ALU (output control)
ALU (LEDs)
REGISTER A
REGISTER B
PROGRAM COUNTER
PROGRAM COUNTER (LEDs)
PROGRAM COUNTER (output control)
REGISTER JUMP
REGISTER MEMORY ADDRESS
RAM
ROM
ROM (LEDs)
REGISTER JUMP (output control)
BUS LEDs
MEM (output control)
ACHTUNG! EIGENTLICH 74FCT2574T => gleiches pinout
INSTRUCTION REGISTER
INSTRUCTION REGISTER (LEDs)
MICRO-INSTRUCTION MANAGER
GFX Matrix
GFX Logic
CLOCK
parallel bus interface
power supply
Aufsteck Clock module => Inverter mit RC Glied
RAM (LEDs)
address space control
excess NAND gates (RAM)
ALU (arithmetic)

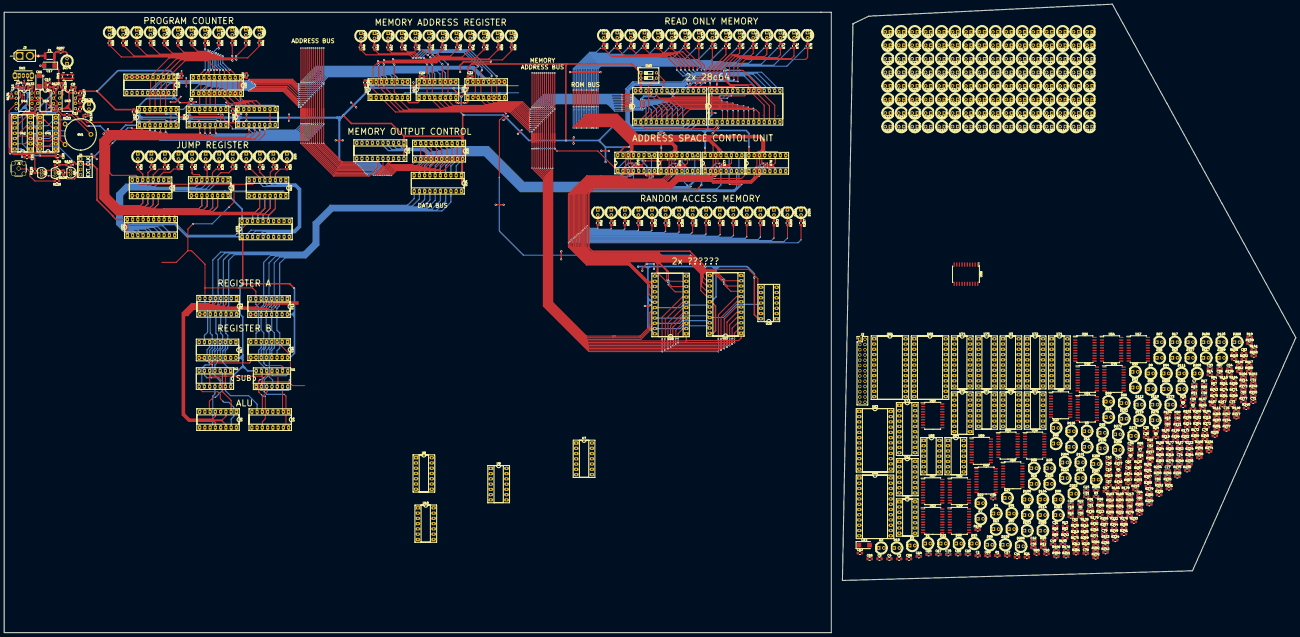
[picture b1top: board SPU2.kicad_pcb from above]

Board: 2 copper layers, 624.6 x 303.9 mm, 736 parts (0 on the bottom side), 669 nets.
